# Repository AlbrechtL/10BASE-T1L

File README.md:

<p class="center"><i>Completed 10BASE-T1L Adapters</i></p>

The final design and production files for the main PCB are in the 'rev3' folder. 

The end plates are in the 'panels' folder.

If you want to build this yourself, you need to buy three parts in addition to having the main PCB assembled by JLCPCB and having JLCPCB fab the end plates:

<ul>
  <li>1x <a href="https://www.digikey.com/en/products/detail/dialight/5151069F/1769784?s=N4IgTCBcDaIKwEZEAYBsBOAYiAugXyA">5151069F light pipe</a></li>
  <li>1x <a href="https://a.co/d/4ymOL0K">Aluminum Enclosure</a></li>
  <li>4x m2.5 pan head screws (the enclosure scomes with flat countersunk head screws which I don't care for)</li>
</ul>

Additional information on this project can be found <a href="http://robruark.com/projects/10BASE-T1L/10BASE-T1L.html">here</a>.

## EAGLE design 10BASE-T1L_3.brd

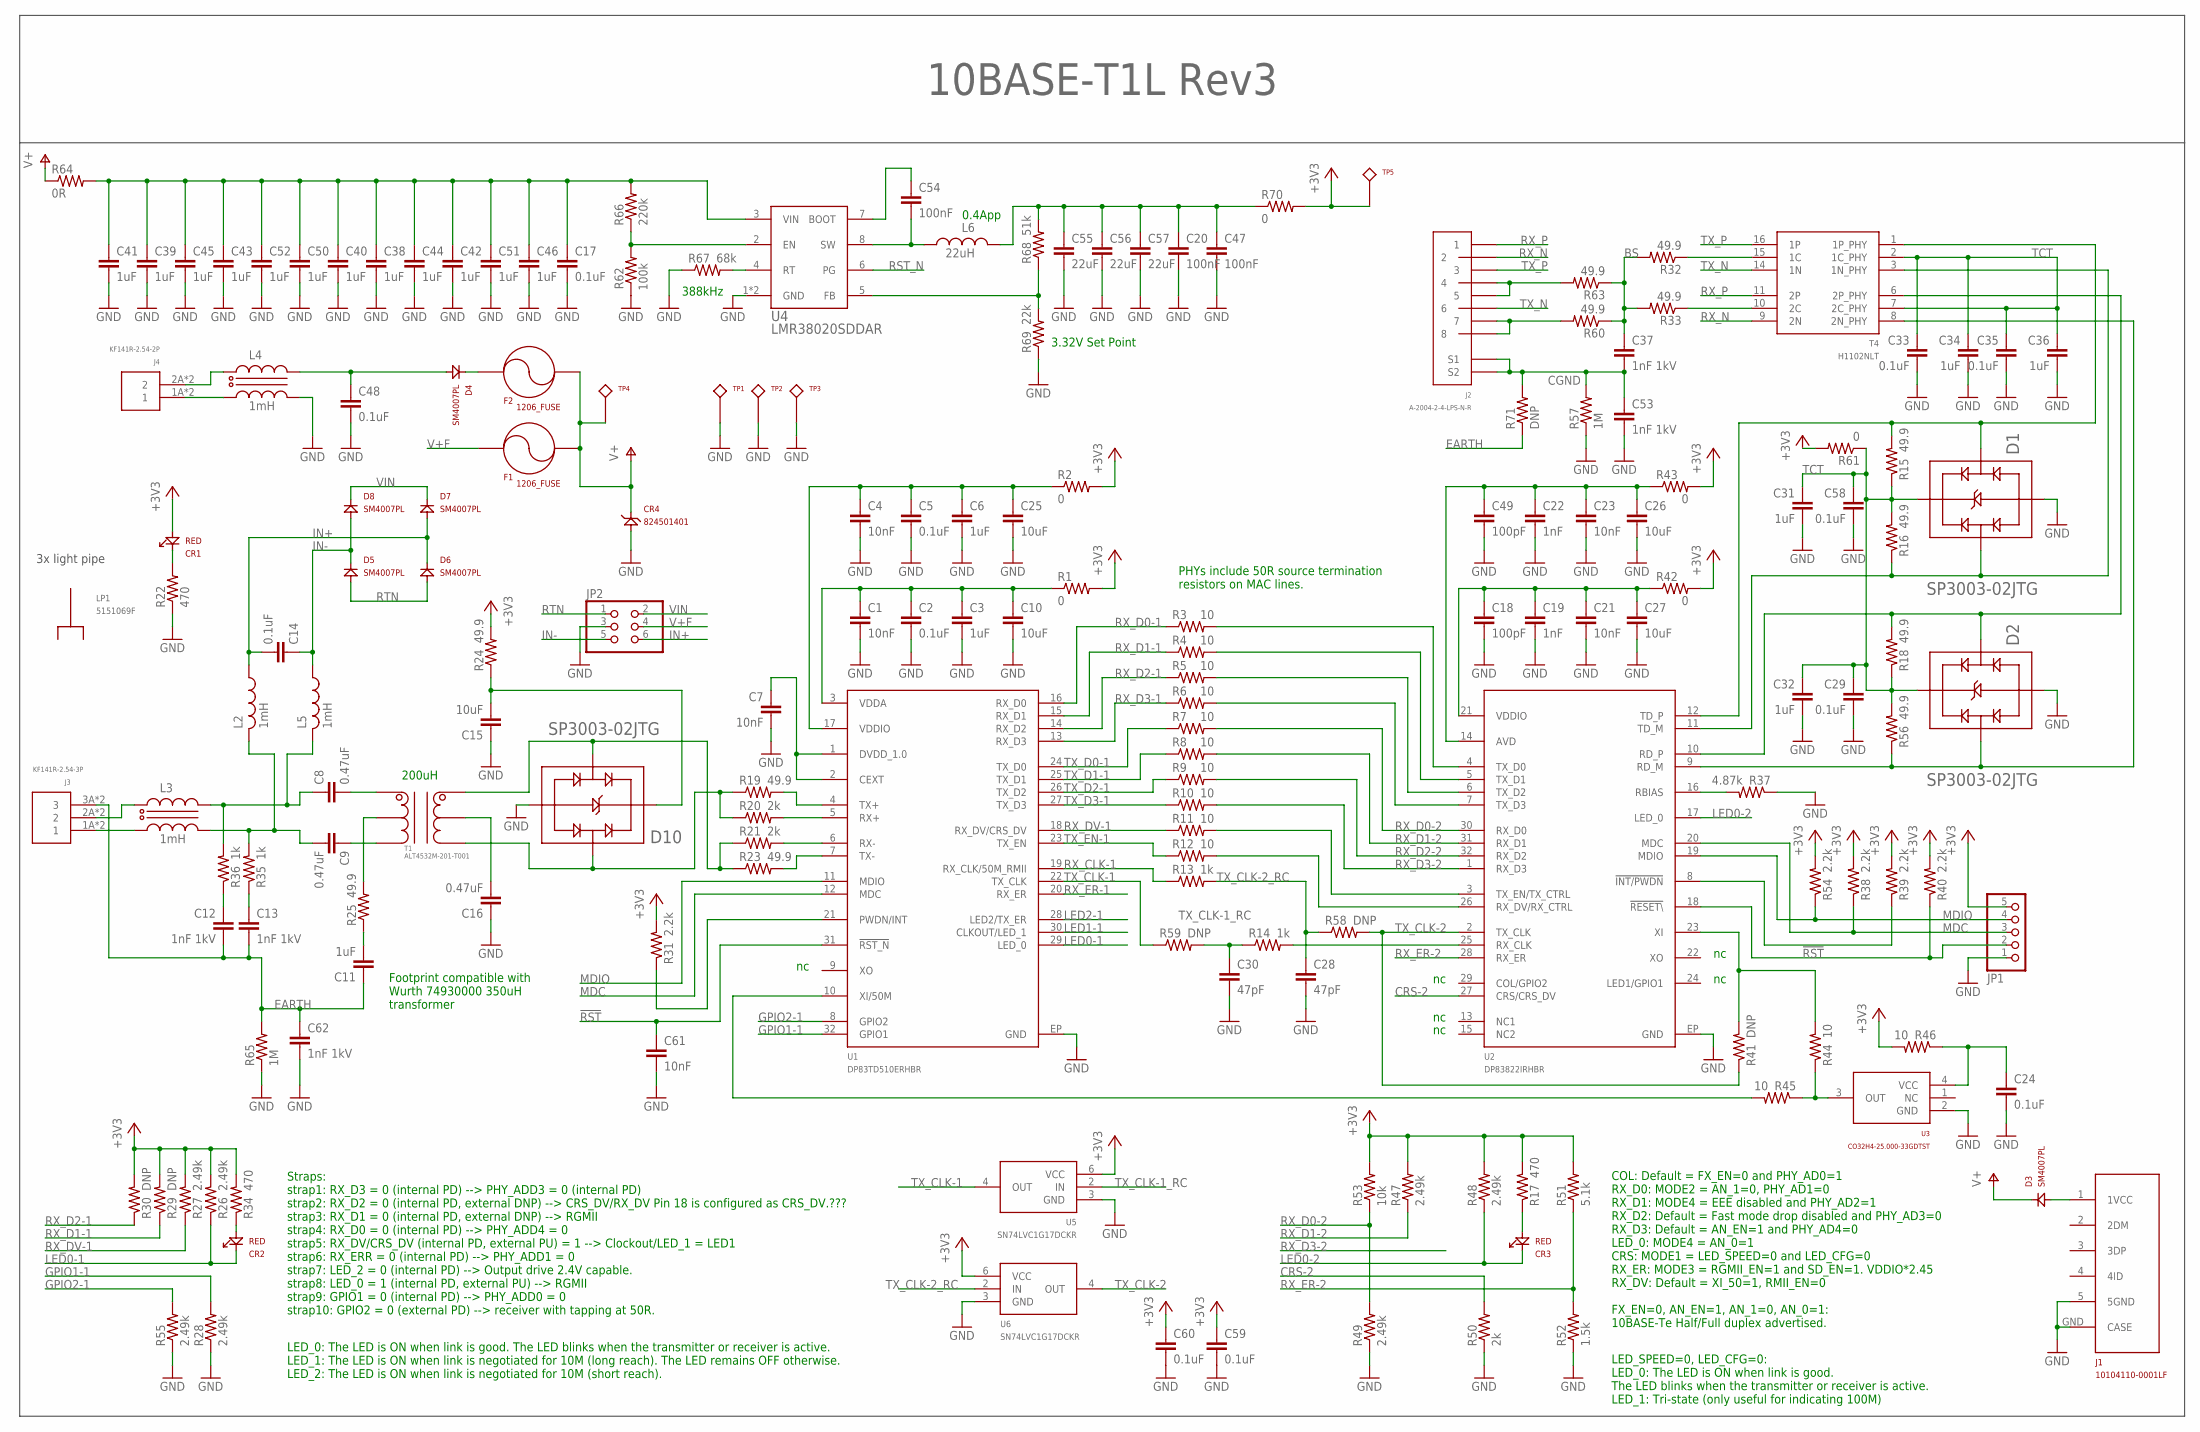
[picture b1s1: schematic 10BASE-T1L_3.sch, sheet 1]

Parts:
C1, C4, C7, C21, C23, C61: 10nF; 0402_INDUCTOR
C2, C5, C24, C29, C33, C35, C58, C59, C60: 0.1uF; 0402_INDUCTOR
C3, C6, C31, C32, C34, C36: 1uF; 0402_INDUCTOR
C8, C9, C16: 0.47uF; 0603
C10, C15, C25, C26, C27: 10uF; 0603
C11: 1uF; 0603
C12, C13, C37, C53, C62: 1nF 1kV; C1206
C14, C17, C48: 0.1uF; 0603
C18, C49: 100pF; 0402_INDUCTOR
C19, C22: 1nF; 0402_INDUCTOR
C20, C47, C54: 100nF; 0603
C28, C30: 47pF; 0402_INDUCTOR
C38, C39, C40, C41, C42, C43, C44, C45, C46, C50, C51, C52: 1uF; C1206
C55, C56, C57: 22uF; C1206
CR1, CR2, CR3: RED; 0603_DIODE
CR4: 824501401; DO-214AC
D1, D2, D10: SP3003-02JTG; SC-70-5
D3, D4, D5, D6, D7, D8: SM4007PL; SOD123(AK)
F1, F2: 1206_FUSE; 1206
J1: 10104110-0001LF; MICRO_USB
J2: A-2004-2-4-LPS-N-R
J3: KF141R-2.54-3P
J4: KF141R-2.54-2P
JP1: PINHD-1X5; 1X05
JP2: PINHD-2X3; 2X03
L2, L5: 1mH; SNR5040
L3, L4: 1mH; SMCM090605
L6: 22uH; TMPC0603H
LP1: 5151069F
R1, R2, R42, R43, R61, R70: 0; 0603
R3, R4, R5, R6, R7, R8, R9, R10, R11, R12, R44, R45, R46: 10; R0402
R13, R14: 1k; R0402
R15, R16, R18, R19, R23, R32, R33, R56, R60, R63: 49.9; R0402
R17, R22, R34: 470; 0603
R20, R21, R50: 2k; R0402
R24, R25: 49.9; 0603
R26, R27, R28, R47, R48, R49, R55: 2.49k; R0402
R29, R30, R41, R58, R59: DNP; R0402
R31, R38, R39, R40, R54: 2.2k; R0402
R35, R36: 1k; 0603
R37: 4.87k; R0402
R51: 5.1k; R0402
R52: 1.5k; R0402
R53: 10k; R0402
R57, R65: 1M; 1206
R62: 100k; 0603
R64: 0R; 1206
R66: 220k; 0603
R67: 68k; 0603
R68: 51k; 0603
R69: 22k; 0603
R71: DNP; 0603
T1: ALT4532M-201-T001; TDK_ALT
T4: H1102NLT
TP1, TP2, TP3: 5011; 5010
TP4, TP5: 5010
U1: DP83TD510ERHBR; QFN32-55_TI
U2: DP83822IRHBR; QFN32-55_TI
U3: CO32H4-25.000-33GDTST; 3.2X2.5_4SMD
U4: LMR38020SDDAR; SOIC8_TP_TI
U5, U6: SN74LVC1G17DCKR; SC-70

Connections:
3V3R: C20.1, C47.1, C55.1, C56.1, C57.1, L6.P$1, R68.2, R70.1
!RST: C61.P$1 (1), JP1.2, R40.1, U1.31 (!RST_N), U2.18 (!RESET\)
+3V3: C59.P$1 (1), C60.P$1 (1), CR1.A, JP1.5, R1.2, R2.2, R17.2, R24.2, R26.2, R27.2, R29.2, R30.2, R31.2, R34.2, R38.2, R39.2, R40.2, R42.2, R43.2, R46.2, R47.2, R48.2, R51.2, R53.2, R54.2, R61.2, R70.2, TP5.P$1, U5.6 (VCC), U6.6 (VCC)
BS: C37.1, R32.2, R33.2, R60.1, R63.1
CEXT_L: C7.P$1 (1), U1.1 (DVDD_1.0), U1.2 (CEXT)
CGND: C37.2, C53.1, J2.S1, J2.S2, R57.2, R71.2
CRS-2: R50.2, U2.27 (CRS/CRS_DV)
EARTH: C11.1, C12.2, C13.2, C62.1, J3.3A (3), J3.3B (3), R65.2, R71.1
GND: C1.P$2 (2), C2.P$2 (2), C3.P$2 (2), C4.P$2 (2), C5.P$2 (2), C6.P$2 (2), C7.P$2 (2), C10.2, C15.1, C16.1, C17.2, C18.P$2 (2), C19.P$2 (2), C20.2, C21.P$2 (2), C22.P$2 (2), C23.P$2 (2), C24.P$2 (2), C25.2, C26.2, C27.2, C28.P$2 (2), C29.P$2 (2), C30.P$2 (2), C31.P$2 (2), C32.P$2 (2), C33.P$2 (2), C34.P$2 (2), C35.P$2 (2), C36.P$2 (2), C38.2, C39.2, C40.2, C41.2, C42.2, C43.2, C44.2, C45.2, C46.2, C47.2, C48.2, C49.P$2 (2), C50.2, C51.2, C52.2, C53.2, C55.2, C56.2, C57.2, C58.P$2 (2), C59.P$2 (2), C60.P$2 (2), C61.P$2 (2), C62.2, CR4.A, D1.2 (GND), D2.2 (GND), D10.2 (GND), J1.5 (5GND), J1.GND (CASE), JP1.1, JP2.3, L4.OUT2 (2OUT), R22.1, R28.1, R37.1, R49.1, R50.1, R52.1, R55.1, R57.1, R62.1, R65.1, R67.1, R69.1, TP1.P$1, TP2.P$1, TP3.P$1, U1.EP (GND), U2.EP (GND), U3.2 (GND), U4.1 (GND), U4.TP (GND), U5.3 (GND), U6.3 (GND)
GPIO1-1: R28.2, U1.32 (GPIO1)
GPIO2-1: R55.2, U1.8 (GPIO2)
IN+: C14.2, D6.K, D7.A, JP2.6, L2.P$1 (1)
IN+L: C9.2, L2.P$2 (2), L3.OUT2 (2OUT), R35.2
IN-: C14.1, D5.K, D8.A, JP2.5, L5.P$1 (1)
IN-L: C8.1, L3.OUT1 (1OUT), L5.P$2 (2), R36.2
LED0-1: CR2.K, R26.1, U1.29 (LED_0)
LED0-2: CR3.K, R48.1, U2.17 (LED_0)
LED1-1: U1.30 (CLKOUT/LED_1)
LED2-1: U1.28 (LED2/TX_ER)
MDC: JP1.3, R38.1, U1.12 (MDC), U2.20 (MDC)
MDIO: JP1.4, R54.1, U1.11 (MDIO), U2.19 (MDIO)
unnamed: C48.1, D4.A, L4.OUT1 (1OUT)
unnamed: C8.2, T1.1
unnamed: CR3.A, R17.1
unnamed: J2.4, J2.5, R63.2
unnamed: J2.7, J2.8, R60.2
unnamed: CR2.A, R34.1
unnamed: R31.1, U1.21 (PWDN/INT)
unnamed: D3.A, J1.1 (1VCC)
unnamed: J4.1A (1), J4.1B (1), L4.IN2 (2IN)
unnamed: R14.2, U2.25 (RX_CLK)
unnamed: C9.1, T1.2 (3)
unnamed: R25.2, T1.6 (2)
unnamed: CR1.K, R22.2
unnamed: D4.K, F2.1
unnamed: R12.2, U2.26 (RX_DV/RX_CTRL)
unnamed: R11.2, U2.3 (TX_EN/TX_CTRL)
unnamed: R62.2, R66.1, U4.2 (EN)
unnamed: R32.1, T4.15 (1C)
unnamed: R6.2, U2.7 (TX_D3)
unnamed: R5.2, U2.6 (TX_D2)
unnamed: R4.2, U2.5 (TX_D1)
unnamed: R3.2, U2.4 (TX_D0)
unnamed: J4.2A (2), J4.2B (2), L4.IN1 (1IN)
unnamed: J3.1A (1), J3.1B (1), L3.IN2 (2IN)
unnamed: C11.2, R25.1
unnamed: R41.2, R44.2, U2.23 (XI)
unnamed: C16.2, T1.3 (5)
unnamed: C12.1, R36.1
unnamed: C13.1, R35.1
unnamed: J3.2A (2), J3.2B (2), L3.IN1 (1IN)
unnamed: C15.2, D10.3 (VCC), R24.1
unnamed: R39.1, U2.8 (!INT/PWDN)
unnamed: R68.1, R69.2, U4.5 (FB)
unnamed: R37.2, U2.16 (RBIAS)
unnamed: R44.1, R45.1, U3.3 (OUT)
unnamed: C24.P$1 (1), R46.1, U3.4 (VCC)
unnamed: R45.2, U1.10 (XI/50M)
unnamed: R33.1, T4.10 (2C)
unnamed: C54.1, U4.7 (BOOT)
unnamed: R67.2, U4.4 (RT)
RD_N: D2.5 (IO1), R56.1, T4.8 (2N_PHY), U2.9 (RD_M)
RD_P: D2.4 (IO2), R18.2, T4.6 (2P_PHY), U2.10 (RD_P)
RST_N: U4.6 (PG)
RTN: D5.A, D6.A, JP2.1
RXR_N: R21.2, U1.6 (RX-)
RXR_P: R20.2, U1.5 (RX+)
RX_CLK-1: R13.1, U1.19 (RX_CLK/50M_RMII)
RX_D0-1: R3.1, U1.16 (RX_D0)
RX_D0-2: R7.2, R49.2, R53.1, U2.30 (RX_D0)
RX_D1-1: R4.1, R29.1, U1.15 (RX_D1)
RX_D1-2: R8.2, R47.1, U2.31 (RX_D1)
RX_D2-1: R5.1, R30.1, U1.14 (RX_D2)
RX_D2-2: R9.2, U2.32 (RX_D2)
RX_D3-1: R6.1, U1.13 (RX_D3)
RX_D3-2: R10.2, U2.1 (RX_D3)
RX_DV-1: R11.1, R27.1, U1.18 (RX_DV/CRS_DV)
RX_ER-1: U1.20 (RX_ER)
RX_ER-2: R51.1, R52.2, U2.28 (RX_ER)
RX_N: J2.2, T4.9 (2N)
RX_P: J2.1, T4.11 (2P)
SW: C54.2, L6.P$2, U4.8 (SW)
T1L_N: D10.5 (IO1), R21.1, R23.1, T1.5 (6)
T1L_P: D10.4 (IO2), R19.1, R20.1, T1.4
TCT: C29.P$1 (1), C31.P$1 (1), C32.P$1 (1), C33.P$1 (1), C34.P$1 (1), C35.P$1 (1), C36.P$1 (1), C58.P$1 (1), D1.3 (VCC), D2.3 (VCC), R15.1, R16.2, R18.1, R56.2, R61.1, T4.2 (1C_PHY), T4.7 (2C_PHY)
TD_N: D1.5 (IO1), R16.1, T4.3 (1N_PHY), U2.11 (TD_M)
TD_P: D1.4 (IO2), R15.2, T4.1 (1P_PHY), U2.12 (TD_P)
TXR_N: R23.2, U1.7 (TX-)
TXR_P: R19.2, U1.4 (TX+)
TX_CLK-1: R59.1, U1.22 (TX_CLK), U5.4 (OUT)
TX_CLK-1_RC: C30.P$1 (1), R14.1, R59.2, U5.2 (IN)
TX_CLK-2: R41.1, R58.2, U2.2 (TX_CLK), U6.4 (OUT)
TX_CLK-2_RC: C28.P$1 (1), R13.2, R58.1, U6.2 (IN)
TX_D0-1: R7.1, U1.24 (TX_D0)
TX_D1-1: R8.1, U1.25 (TX_D1)
TX_D2-1: R9.1, U1.26 (TX_D2)
TX_D3-1: R10.1, U1.27 (TX_D3)
TX_EN-1: R12.1, U1.23 (TX_EN)
TX_N: J2.6, T4.14 (1N)
TX_P: J2.3, T4.16 (1P)
V+: CR4.C (K), D3.K, F1.2, F2.2, R64.1, TP4.P$1
V+F: F1.1, JP2.4
V+R: C17.1, C38.1, C39.1, C40.1, C41.1, C42.1, C43.1, C44.1, C45.1, C46.1, C50.1, C51.1, C52.1, R64.2, R66.2, U4.3 (VIN)
VDDA_L: C1.P$1 (1), C2.P$1 (1), C3.P$1 (1), C10.1, R1.1, U1.3 (VDDA)
VDDA_L1: C18.P$1 (1), C19.P$1 (1), C21.P$1 (1), C27.1, R42.1, U2.21 (VDDIO)
VDDIO_L: C4.P$1 (1), C5.P$1 (1), C6.P$1 (1), C25.1, R2.1, U1.17 (VDDIO)
VDDIO_L1: C22.P$1 (1), C23.P$1 (1), C26.1, C49.P$1 (1), R43.1, U2.14 (AVD)
VIN: D7.K, D8.K, JP2.2

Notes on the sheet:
Straps: strap1: RX_D3 = 0 (internal PD) --> PHY_ADD3 = 0 (internal PD) strap2: RX_D2 = 0 (internal PD, external DNP) --> CRS_DV/RX_DV Pin 18 is configured as CRS_DV.??? strap3: RX_D1 = 0 (internal PD, external DNP) --> RGMII strap4: RX_D0 = 0 (internal PD) --> PHY_ADD4 = 0 strap5: RX_DV/CRS_DV (int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
LED_0: The LED is ON when link is good. The LED blinks when the transmitter or receiver is active. LED_1: The LED is ON when link is negotiated for 10M (long reach). The LED remains OFF otherwise. LED_2: The LED is ON when link is negotiated for 10M (short reach).
LED_SPEED=0, LED_CFG=0: LED_0: The LED is ON when link is good. The LED blinks when the transmitter or receiver is active. LED_1: Tri-state (only useful for indicating 100M)
COL: Default = FX_EN=0 and PHY_AD0=1 RX_D0: MODE2 = AN_1=0, PHY_AD1=0 RX_D1: MODE4 = EEE disabled and PHY_AD2=1 RX_D2: Default = Fast mode drop disabled and PHY_AD3=0 RX_D3: Default = AN_EN=1 and PHY_AD4=0 LED_0: MODE4 = AN_0=1 CRS: MODE1 = LED_SPEED=0 and LED_CFG=0 RX_ER: MODE3 = RGMII_EN=1 and SD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
3x light pipe
10BASE-T1L Rev3
388kHz
0.4App
3.32V Set Point
PHYs include 50R source termination resistors on MAC lines.
200uH
Footprint compatible with Wurth 74930000 350uH transformer

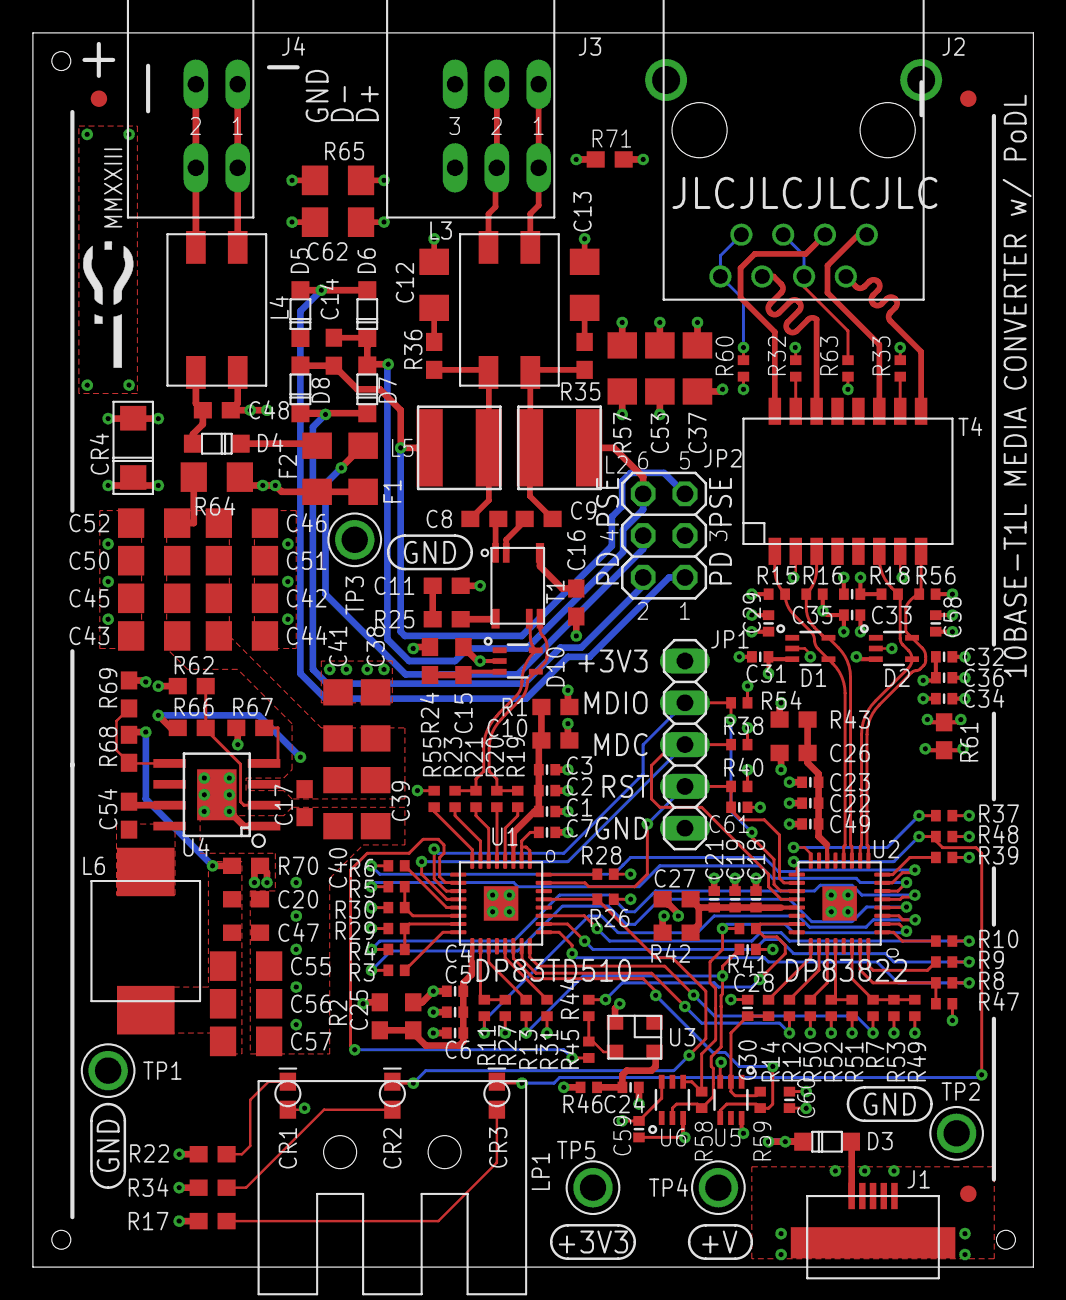
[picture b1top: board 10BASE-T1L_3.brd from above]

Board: 4 copper layers, 60.8 x 75.0 mm, 173 parts (0 on the bottom side), 104 nets.

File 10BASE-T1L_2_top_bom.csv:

Comment,Designator,Footprint,LCSC Part #
0,R1 R2 R42 R43 R61 R70,603,
0.1uF,C2 C5,0402_INDUCTOR,
0.1uF,C14 C17,603,
0.1uF,C24 C29 C33 C35,0402_INDUCTOR,
0.1uF,C48,603,
0.1uF,C58 C59 C60,0402_INDUCTOR,
0.47uF,C8 C9 C16,603,
0R,R64,1206,
1.5k,R52,R0402,
1M,R57 R65,1206,
1k,R13 R14,R0402,
1k,R35 R36,603,
1mH,L1 L3 L4,SMCM090605,C1692756
1nF,C19 C22,0402_INDUCTOR,
1nF 1kV,C12 C13 C37 C53 C62,C1206,
1uF,C3 C6,0402_INDUCTOR,
1uF,C11,603,
1uF,C31 C32 C34 C36,0402_INDUCTOR,
1uF,C38 C39 C40 C41 C42 C43 C44 C45 C46 C50 C51 C52,C1206,
2.2k,R31 R38 R39 R40 R54,R0402,
2.49k,R26 R27 R28 R47 R48 R49 R55,R0402,
2k,R20 R21 R50,R0402,
4.87k,R37,R0402,
5.1k,R51,R0402,
10,R3 R4 R5 R6 R7 R8 R9 R10 R11 R12 R44 R45 R46,R0402,
10k,R53,R0402,
10nF,C1 C4 C7 C21 C23 C61,0402_INDUCTOR,
10uF,C10 C15 C25 C26 C27,603,
22k,R68,603,
22uF,C55 C56 C57,C1206,
22uH,L6,TMPC0603H,C357197
47pF,C28 C30,0402_INDUCTOR,
49.9,R15 R16 R18 R19 R23,R0402,
49.9,R24 R25,603,
49.9,R32 R33 R56 R60 R63,R0402,
51k,R69,603,
68k,R67,603,
100k,R62,603,
100nF,C20 C47 C54,603,
100pF,C18 C49,0402_INDUCTOR,
220k,R66,603,
470,R17 R22 R34,603,
1206_FUSE,F1 F2,1206,C207239
10104110-0001LF,J1,MICRO_USB,C2931352
824501401,CR4,DO-214AC,C148235
ALT4532M-201-T001,T1,TDK_ALT,C2845101
CO32H4-25.000-33GDTST,U3,3.2X2.5_4SMD,C5185361
DNP,R29 R30 R41 R58 R59,R0402,
DNP,R71,603,
DP83TD510ERHBR,U1,QFN32-55_TI,C2862898
DP83822IRHBR,U2,QFN32-55_TI,C601649
H1102NLT,T4,H1102NLT,C18584
LMR38020SDDAR,U4,SOIC8_TP_TI,C3192337
GREEN,CR2 CR3,0603_DIODE,C72043
RED,CR1,0603_DIODE,C2286
SM4007PL,D3 D4 D5 D6 D7 D8,SOD123(AK),C64898
SN74LVC1G17DCKR,U5 U6,SC-70,C10425
SP3003-02JTG,D1 D2 D10,SC-70-5,C151302
DNP,JP1,5-pin,
210-82-03GB01,JP2,6-pin,C390684
HC-RJ45-5622-1-4,J2,,C3010550
KF141R-2.54-3P,J3,,C475125
KF141R-2.54-2P,J4,,C475124

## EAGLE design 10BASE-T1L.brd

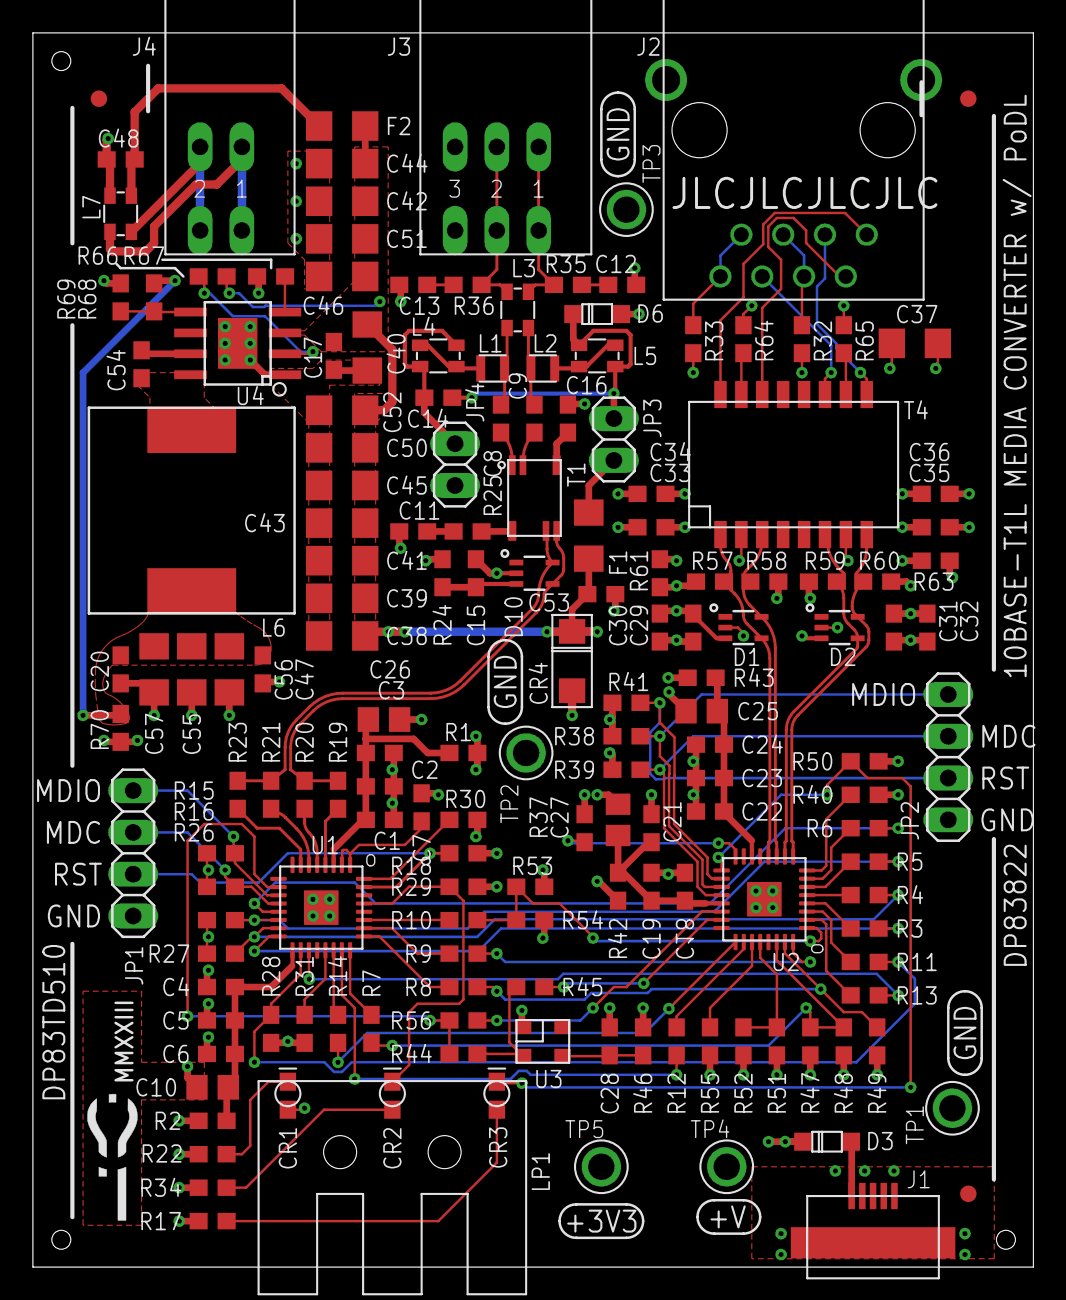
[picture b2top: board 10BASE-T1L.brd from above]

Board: 4 copper layers, 60.8 x 75.0 mm, 163 parts (0 on the bottom side), 103 nets.

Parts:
C1, C4, C7, C21, C24: 10nF; 0603
C2, C5, C20, C28, C30, C32, C33, C35, C47, C53, C54: 100nF; 0603
C3, C6, C11, C29, C31, C34, C36: 1uF; 0603
C8, C9, C16: 0.47uF; 0603
C10, C25, C26, C27: 10uF; 0805
C12, C13, C14, C17, C48: 0.1uF; 0603
C15: 10uF; 0603
C18, C22: 100pF; 0603
C19, C23: 1nF; 0603
C37: 1nF 1kV; C1206
C38, C39, C40, C41, C42, C43, C44, C45, C46, C50, C51, C52: 1uF; C1206
C55, C56, C57: 22uF; C1206
CR1, CR2, CR3: RED; 0603_DIODE
CR4: 824501401; DO-214AC
D1, D2, D10: SP3003-02JTG; SC-70-5
D3, D6: SM4007PL; SOD123(AK)
F1, F2: 1206_FUSE; 1206
J1: 10104110-0001LF; MICRO_USB
J2: A-2004-2-4-LPS-N-R
J3: TBL009-254-03GY-2GY
J4: TBL009-254-02GY-2GY
JP1, JP2: 1X04
JP3, JP4: 1X02
L1, L2: 33uH; 0806
L3, L4, L5, L7: 0.33uH; SDCW2520
L6: 22uH; APW12A10
LP1: 5151069F
R1, R2, R42, R43, R61, R63, R70: 0; 0603
R3, R4, R5, R6, R7, R8, R9, R10, R11, R12, R13, R14, R44, R45, R46, R66: 10; 0603
R15, R16, R18, R31, R38, R39, R40, R41: 2.2k; 0603
R17, R34: 470; 0603
R19, R23, R24, R25, R57, R58, R59, R60: 49.9; 0603
R20, R21: 2k; 0603
R22: 499; 0603
R26, R27, R53, R54, R56: DNP; 0603
R28, R29, R30, R48, R49, R50: 2.49k; 0603
R32, R33, R64, R65: 75; 0603
R35, R36: 1k; 0603
R37: 4.87k; 0603
R47: 10k; 0603
R51: 6.2k; 0603
R52, R55: 1.96k; 0603
R67: 64.9k; 0603
R68: 100k; 0603
R69: 24.9k; 0603
T1: ALT4532M-201-T001; TDK_ALT
T4: H1102NLT
TP1, TP2, TP3: 5011; 5010
TP4, TP5: 5010
U1: DP83TD510ERHBR; QFN32-55_TI
U2: DP83822IRHBR; QFN32-55_TI
U3: CO32H4-25.000-33GDTST; 3.2X2.5_4SMD
U4: LMR38020SDDAR; SOIC8_TP_TI

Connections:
3V3R: C20.1, C47.1, C55.1, C56.1, C57.1, L6.P$2, R68.2, R70.1
+3V3: CR1.A, R1.2, R2.2, R15.2, R16.2, R17.2, R18.2, R24.2, R26.2, R27.2, R28.2, R29.2, R31.2, R34.2, R38.2, R39.2, R40.2, R41.2, R42.2, R43.2, R46.2, R47.2, R49.2, R50.2, R51.2, R53.2, R61.2, R63.1, R70.2, TP5.P$1
BS: C37.1, R32.2, R33.2, R64.1, R65.1
CEXT_L: C7.1, U1.1, U1.2
CGND: C37.2, J2.S1, J2.S2
CRS-2: R55.2, U2.27
GND: C1.2, C2.2, C3.2, C4.2, C5.2, C6.2, C7.2, C10.2, C11.1, C12.1, C13.1, C15.1, C16.1, C17.2, C18.2, C19.2, C20.2, C21.2, C22.2, C23.2, C24.2, C25.2, C26.2, C27.2, C28.2, C29.1, C30.1, C31.1, C32.1, C33.1, C34.1, C35.1, C36.1, C38.2, C39.2, C40.2, C41.2, C42.2, C43.2, C44.2, C45.2, C46.2, C47.2, C48.2, C50.2, C51.2, C52.2, C53.2, C55.2, C56.2, C57.2, CR4.A, D1.2, D2.2, D6.A, D10.2, J1.5, J1.GND, J3.3A, J3.3B, JP1.1, JP2.1, JP4.2, L7.B2, R22.1, R30.2, R37.2, R48.1, R52.1, R54.1, R55.1, R67.1, R69.1, TP1.P$1, TP2.P$1, TP3.P$1, U1.EP, U2.EP, U3.2, U4.1, U4.TP
GPIO1-1: R30.1, U1.32
LED0-1: CR2.K, R29.1, U1.29
LED0-2: CR3.K, R50.1, U2.17
unnamed: C48.1, F2.1, L7.A2
unnamed: C8.2, T1.1
unnamed: CR3.A, R17.1
unnamed: J2.4, J2.5, R32.1
unnamed: J2.7, J2.8, R33.1
unnamed: CR2.A, R34.1
unnamed: JP1.4, R15.1, U1.11
unnamed: JP1.3, R16.1, U1.12
unnamed: R31.1, U1.21
unnamed: D3.A, J1.1
unnamed: R56.2, U2.22
unnamed: J4.1A, J4.1B, L7.B1
unnamed: R14.2, U2.25
unnamed: C9.1, T1.2
unnamed: R25.2, T1.6
unnamed: C8.1, L1.P$2, L3.A2
unnamed: C9.2, L2.P$2, L3.B2
unnamed: CR1.K, R22.2
unnamed: L1.P$1, L4.A2, L4.B1
unnamed: L2.P$1, L5.A1, L5.B2
unnamed: R13.2, U2.2
unnamed: R12.2, U2.26
unnamed: R11.2, U2.3
unnamed: C14.2, D6.K, JP3.1, L5.A2, L5.B1
unnamed: C14.1, JP4.1, L4.A1, L4.B2
unnamed: R64.2, T4.15
unnamed: R6.2, U2.7
unnamed: R5.2, U2.6
unnamed: R4.2, U2.5
unnamed: R3.2, U2.4
unnamed: J4.2A, J4.2B, L7.A1
unnamed: F1.1, JP3.2
unnamed: J3.1A, J3.1B, L3.B1, R35.2
unnamed: C11.2, R25.1
unnamed: C16.2, T1.3
unnamed: R45.2, U2.23
unnamed: C13.2, R36.1
unnamed: C12.2, R35.1
unnamed: J3.2A, J3.2B, L3.A1, R36.2
unnamed: C15.2, D10.3, R24.1
unnamed: JP2.3, R39.1, U2.20
unnamed: JP2.4, R38.1, U2.19
unnamed: R40.1, U2.8
unnamed: R68.1, R69.2, U4.5
unnamed: R37.1, U2.16
unnamed: R44.2, R45.1, U3.3
unnamed: C28.1, R46.1, U3.4
unnamed: R44.1, R56.1, U1.10
unnamed: R65.2, T4.10
unnamed: C54.1, U4.7
unnamed: R67.2, U4.4
unnamed: R66.2, U4.2
RD_N: D2.5, R60.1, T4.8, U2.9
RD_P: D2.4, R59.2, T4.6, U2.10
RST_N-1: JP1.2, R18.1, U1.31
RST_N-2: JP2.2, R41.1, U2.18
RX+: J2.3, T4.9
RX-: J2.6, T4.11
RXR_N: R21.2, U1.6
RXR_P: R20.2, U1.5
RX_CLK-1: R13.1, U1.19
RX_D0-1: R3.1, U1.16
RX_D0-2: R7.2, R47.1, R48.2, U2.30
RX_D1-1: R4.1, R27.1, U1.15
RX_D1-2: R8.2, R49.1, U2.31
RX_D2-1: R5.1, R26.1, U1.14
RX_D2-2: R9.2, U2.32
RX_D3-1: R6.1, U1.13
RX_D3-2: R10.2, R53.1, R54.2, U2.1
RX_DV-1: R11.1, R28.1, U1.18
RX_ER-2: R51.1, R52.2, U2.28
SW: C54.2, L6.P$1, U4.8
T1L_N: D10.5, R21.1, R23.1, T1.5
T1L_P: D10.4, R19.1, R20.1, T1.4
TCT: C33.2, C34.2, C35.2, C36.2, R63.2, T4.2, T4.7
TCT2: C29.2, C30.2, C31.2, C32.2, D1.3, D2.3, R57.1, R58.2, R59.1, R60.2, R61.1
TD_N: D1.5, R58.1, T4.3, U2.11
TD_P: D1.4, R57.2, T4.1, U2.12
TX+: J2.1, T4.16
TX-: J2.2, T4.14
TXR_N: R23.2, U1.7
TXR_P: R19.2, U1.4
TX_CLK-1: R14.1, U1.22
TX_D0-1: R7.1, U1.24
TX_D1-1: R8.1, U1.25
TX_D2-1: R9.1, U1.26
TX_D3-1: R10.1, U1.27
TX_EN-1: R12.1, U1.23
V+: C17.1, C38.1, C39.1, C40.1, C41.1, C42.1, C43.1, C44.1, C45.1, C46.1, C50.1, C51.1, C52.1, C53.1, CR4.C, D3.K, F1.2, F2.2, R66.1, TP4.P$1, U4.3
VDDA_L: C1.1, C2.1, C3.1, C26.1, R1.1, U1.3
VDDA_L1: C18.1, C19.1, C21.1, C27.1, R42.1, U2.21
VDDIO_L: C4.1, C5.1, C6.1, C10.1, R2.1, U1.17
VDDIO_L1: C22.1, C23.1, C24.1, C25.1, R43.1, U2.14

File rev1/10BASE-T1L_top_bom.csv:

Comment,Designator,Footprint,LCSC Part #
0,R1 R2 R42 R43 R61 R63 R70,603,
0.1uF,C12 C13 C14 C17 C48,603,
0.33uH,L3 L4 L5 L7,SDCW2520,C843574
0.47uF,C8 C9 C16,603,
1.96k,R52 R55,603,C3016159
1k,R35 R36,603,
1nF,C19 C23,603,
1nF 1kV,C37,C1206,C9196
1uF,C3 C6 C11 C29 C31 C34 C36,603,
1uF,C38 C39 C40 C41 C42 C43 C44 C45 C46 C50 C51 C52,C1206,
2.2k,R15 R16 R18 R31 R38 R39 R40 R41,603,
2.49k,R28 R29 R30 R48 R49 R50,603,
2k,R20 R21,603,
4.87k,R37,603,
6.2k,R51,603,
10,R3 R4 R5 R6 R7 R8 R9 R10 R11 R12 R13 R14 R44 R45 R46 R66,603,
10k,R47,603,
10nF,C1 C4 C7 C21 C24,603,
10uF,C10,805,
10uF,C15,603,
10uF,C25 C26 C27,805,
22uF,C55 C56 C57,C1206,
22uH,L6,APW12A10,C311499
24.9k,R69,603,
33uH,L1 L2,806,C5179456
49.9,R19 R23 R24 R25 R57 R58 R59 R60,603,
64.9k,R67,603,
75,R32 R33 R64 R65,603,
100k,R68,603,
100nF,C2 C5 C20 C28 C30 C32 C33 C35 C47 C53 C54,603,
100pF,C18 C22,603,
470,R17 R34,603,
499,R22,603,
1206_FUSE,F1 F2,1206,C207239
10104110-0001LF,J1,MICRO_USB,C2931352
824501401,CR4,DO-214AC,
ALT4532M-201-T001,T1,TDK_ALT,C2845101
CO32H4-25.000-33GDTST,U3,3.2X2.5_4SMD,C5185361
DNP,R26 R27 R53 R54 R56,603,
DP83TD510ERHBR,U1,QFN32-55_TI,C2862898
DP83822IRHBR,U2,QFN32-55_TI,C601649
H1102NLT,T4,H1102NLT,C18584
LMR38020SDDAR,U4,SOIC8_TP_TI,C3192337
GREEN,CR2 CR3,0603_DIODE,C2297
RED,CR1,0603_DIODE,C2286
SM4007PL,D3 D6,SOD123(AK),C64898
SP3003-02JTG,D1 D2 D10,SC-70-5,C151302

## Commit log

2023-10-01 adding reset cap
2023-10-02 Added PD detection
2023-10-08 Rev2
    Fixed RGMII clock
    Fixed LED package
    Fixed 3.3V PoL output voltage
    Fixed oscillator footprint
    Fixed PoDl
    Switched to JLC Available connectors
2023-10-10 Added front / back plates
2023-10-17 Loss calculations
2023-10-22 Adding measurements
2023-11-10 updating images
2024-01-02 Adding V3 with inductor PoDL
2024-06-14 V3 Updates
2024-06-15 Reorganized project
2024-06-15 adding images
